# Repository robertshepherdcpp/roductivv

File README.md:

# roductivv

**a project to help you regain your time and gain focus!**

**Inspiration/Motivation for building this project**
- i always find myself procrastinating when doing tasks, i know there are apps to do this, but then my phone becomes the distraction and I immediately go onto reels
- so i thought it would be good if i something physical that kept me focused.

**what is this project**
- this project is a tool used to help people become *productive*!
- Gamifies doing tasks like *coding*, *studying* and then punishes activities like *gaming* and *scrolling*!
- This is done via a points based system, where certain activities can earn/loose points.
- Gaining points gets you to different milstones (like 100/250/500/10000) etc..

**how to use**
- first get the pcb and case printed
- then insert the pcb into the case
- add the cherry keys and keycaps
- screw the lid on (using the bolts as shown in the BOM)
- then before flashing to the esp, you need to change the SSID and password in the .ino file to be your own, so that the esp can tell the time (synced with wifi)
- then flash (easiest with the arduino ide), and keeped plugged in and then run!
- there are no batteries, so the connection with the esp must be kept.
- the additional bits on the lid that go down are so that the pcb is fixed in place and doesnt move around

**screenshots of the project**
the 3d design:

the schematic:

the footprint:

**BOM**
- Total cost of this project: $41.12.
- All the costs can be seen in the BOM.csv (in this repository)

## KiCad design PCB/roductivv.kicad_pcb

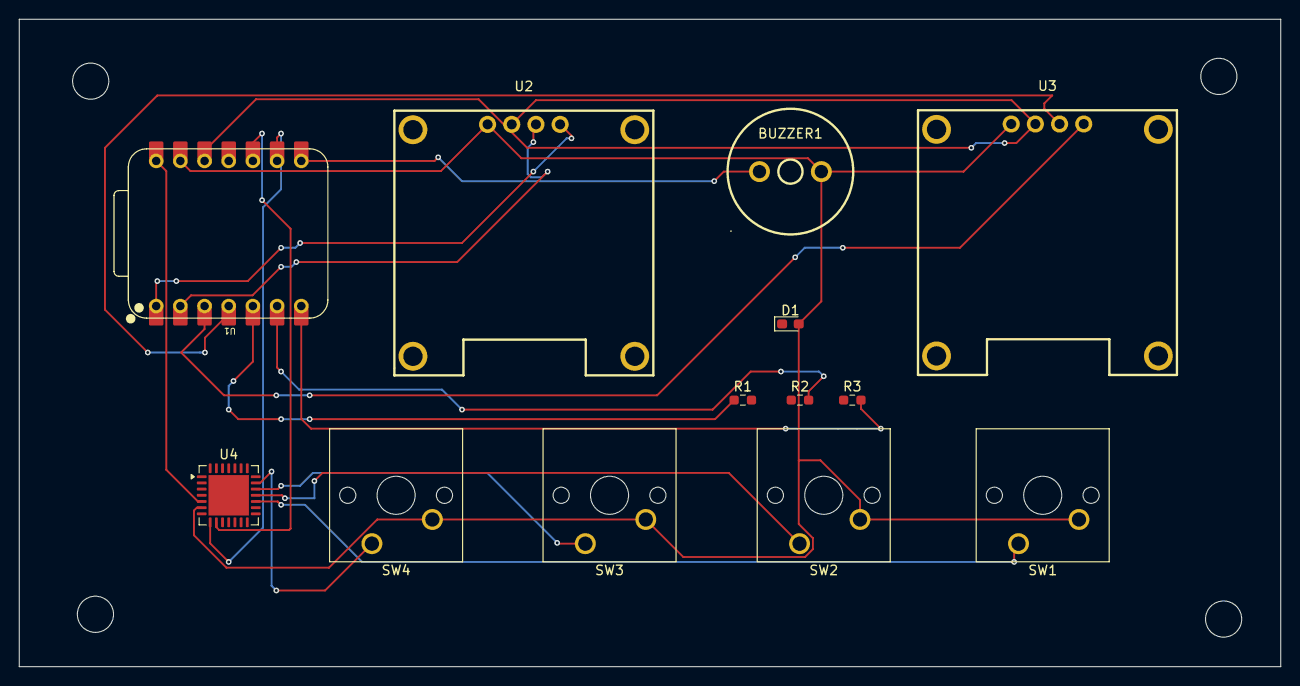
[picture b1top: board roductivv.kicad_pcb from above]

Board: 2 copper layers, 132.5 x 68.0 mm, 13 parts (0 on the bottom side), 17 nets.

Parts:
BUZZER1: 1207-P6.5MM; BUZ-TH_BD12.5-P6.50-D1.4
D1: LED_RGB; LED_0603_1608Metric_Pad1.05x0.95mm_HandSolder
R1, R2, R3: 15; R_0603_1608Metric_Pad0.98x0.95mm_HandSolder
SW1, SW2, SW3, SW4: SW_Push; SW_Cherry_MX_1.00u_PCB
U1: XIAO-ESP32-C6-DIP
U2, U3: HS96L03W2C03; OLED-TH_L27.8-W27.2-P2.54_C9900033791
U4: MCP23017_ML; QFN-28-1EP_6x6mm_P0.65mm_EP4.25x4.25mm

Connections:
+3.3V: U1.12 (3V3), U2.2 (VCC), U3.2 (VCC)
+5V: U1.14 (VBUS), U4.5 (VDD)
GND: BUZZER1.2 (-), D1.2 (GK), SW1.2, SW2.2, SW3.2, SW4.2, U1.13 (GND), U2.1 (GND), U3.1 (GND), U4.6 (VSS)
unnamed: BUZZER1.1 (+), U1.8 (GPIO17_D7_RX)
unnamed: U1.1 (GPIO0_A0_D0), U2.4 (SDA)
unnamed: U1.2 (GPIO1_A1_D1), U2.3 (SCL)
unnamed: U1.3 (GPIO2_A2_D2), U3.4 (SDA)
unnamed: R3.2, U1.7 (GPIO16_D6_TX)
unnamed: U1.9 (GPIO19_D8_SCK), U4.8 (SCK)
unnamed: U1.10 (GPIO20_D9_MISO), U4.9 (SDA)
unnamed: U1.4 (GPIO21_D3), U3.3 (SCL)
unnamed: R1.1, U1.5 (GPIO22_D4_SDA)
unnamed: R2.2, U1.6 (GPIO23_D5_SCL)
unnamed: SW1.1, U4.17 (GPA0)
unnamed: SW2.1, U4.18 (GPA1)
unnamed: SW3.1, U4.19 (GPA2)
unnamed: SW4.1, U4.20 (GPA3)

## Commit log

2026-04-20 add pcb files
2026-04-23 Enhance README with project overview and images
    Added project details, inspiration, process, and images.
2026-04-24 Add BOM.csv with item details and pricing
2026-04-24 Update README with project cost information
    Added cost details and BOM reference to README.
2026-04-24 Change MCP23017 price and supplier
    Updated MCP23017 price and source link.
2026-04-24 Update README with usage instructions and assembly steps
    Added usage instructions for the project, including assembly steps and firmware setup.
2026-04-25 Add RGB LED entry to BOM
2026-04-25 Update README with Zine information
    Added a section about the Zine and its PDF location.
2026-04-25 Rename Untitled (4).pdf to Zine/zine.pdf
2026-04-25 Add resistors entry to BOM.csv
2026-04-25 add gerber files
2026-04-25 Rename roductivv-B_Cu.zip to Gerber/gerber.zip
2026-04-25 Rename roductivv.kicad_pcb to PCB/roductivv.kicad_pcb
2026-04-25 Rename roductivv.kicad_prl to PCB/roductivv.kicad_prl
2026-04-25 Rename roductivv.kicad_pro to PCB/roductivv.kicad_pro
2026-04-25 Rename roductivv.kicad_sch to PCB/roductivv.kicad_sch
2026-04-25 Rename roductivv.step to PCB/roductivv.step
2026-04-25 try add it again
2026-04-25 Rename da_code.ino to Firmware/da_code.ino
2026-04-25 Rename library.txt to library/library.txt
2026-04-25 add library files
2026-04-28 Update README to remove wheels description
    Removed description of wheels from design considerations.
2026-04-28 Fix wording in README about project case
    Removed redundant wording about the case on wheels in the README.
2026-04-28 add the case file
2026-04-28 Rename roductivv.f3d to CAD/roductivv.f3d
2026-04-28 Document building process on YouTube
    Added link to YouTube channel documenting the building process.
2026-05-08 add the step file for the project.
2026-05-08 Rename roductivv.step to CAD/roductivv.step
2026-05-08 Revise README with project details and BOM
    Updated project description and added BOM section.
2026-05-08 trying to make the readme better.
2026-05-08 Update BOM.csv with new items
    Added new items 'Cherry MX keys' and 'Cherry MX keycaps' to BOM.
2026-05-08 Fix formatting for Cherry MX keys and keycaps entries
2026-05-08 Update project cost in README
2026-05-08 Add new image to README.md
2026-05-08 Update usage instructions in README
    Added instructions for adding cherry keys and keycaps.
2026-05-08 add the updated 3d models.
2026-05-08 Add image and project motivation to README
    Updated the README to include a new image and added motivation for the project.
2026-05-08 Update README with new image and project motivation
    Added a new image and updated project motivation.
2026-05-08 add the updated zine
2026-05-08 Rename roductivv.pdf to Zine/roductivv.pdf
2026-06-04 add updated zine
2026-06-04 add the microcontroller cad file
2026-06-04 Clarify lid design purpose in README
    Added clarification about the lid's additional bits for PCB stability.
2026-06-10 Update BOM.csv with new component details
2026-06-10 add the new gerber files.
2026-06-10 add the updated pcb editor screenshot.
2026-06-10 add updated pcb files.
2026-06-10 add the pcb 3d model
2026-06-10 add the updated step file.
2026-06-10 add the updated fusion file.
2026-06-10 add the updated zine.
2026-06-10 updated zine
